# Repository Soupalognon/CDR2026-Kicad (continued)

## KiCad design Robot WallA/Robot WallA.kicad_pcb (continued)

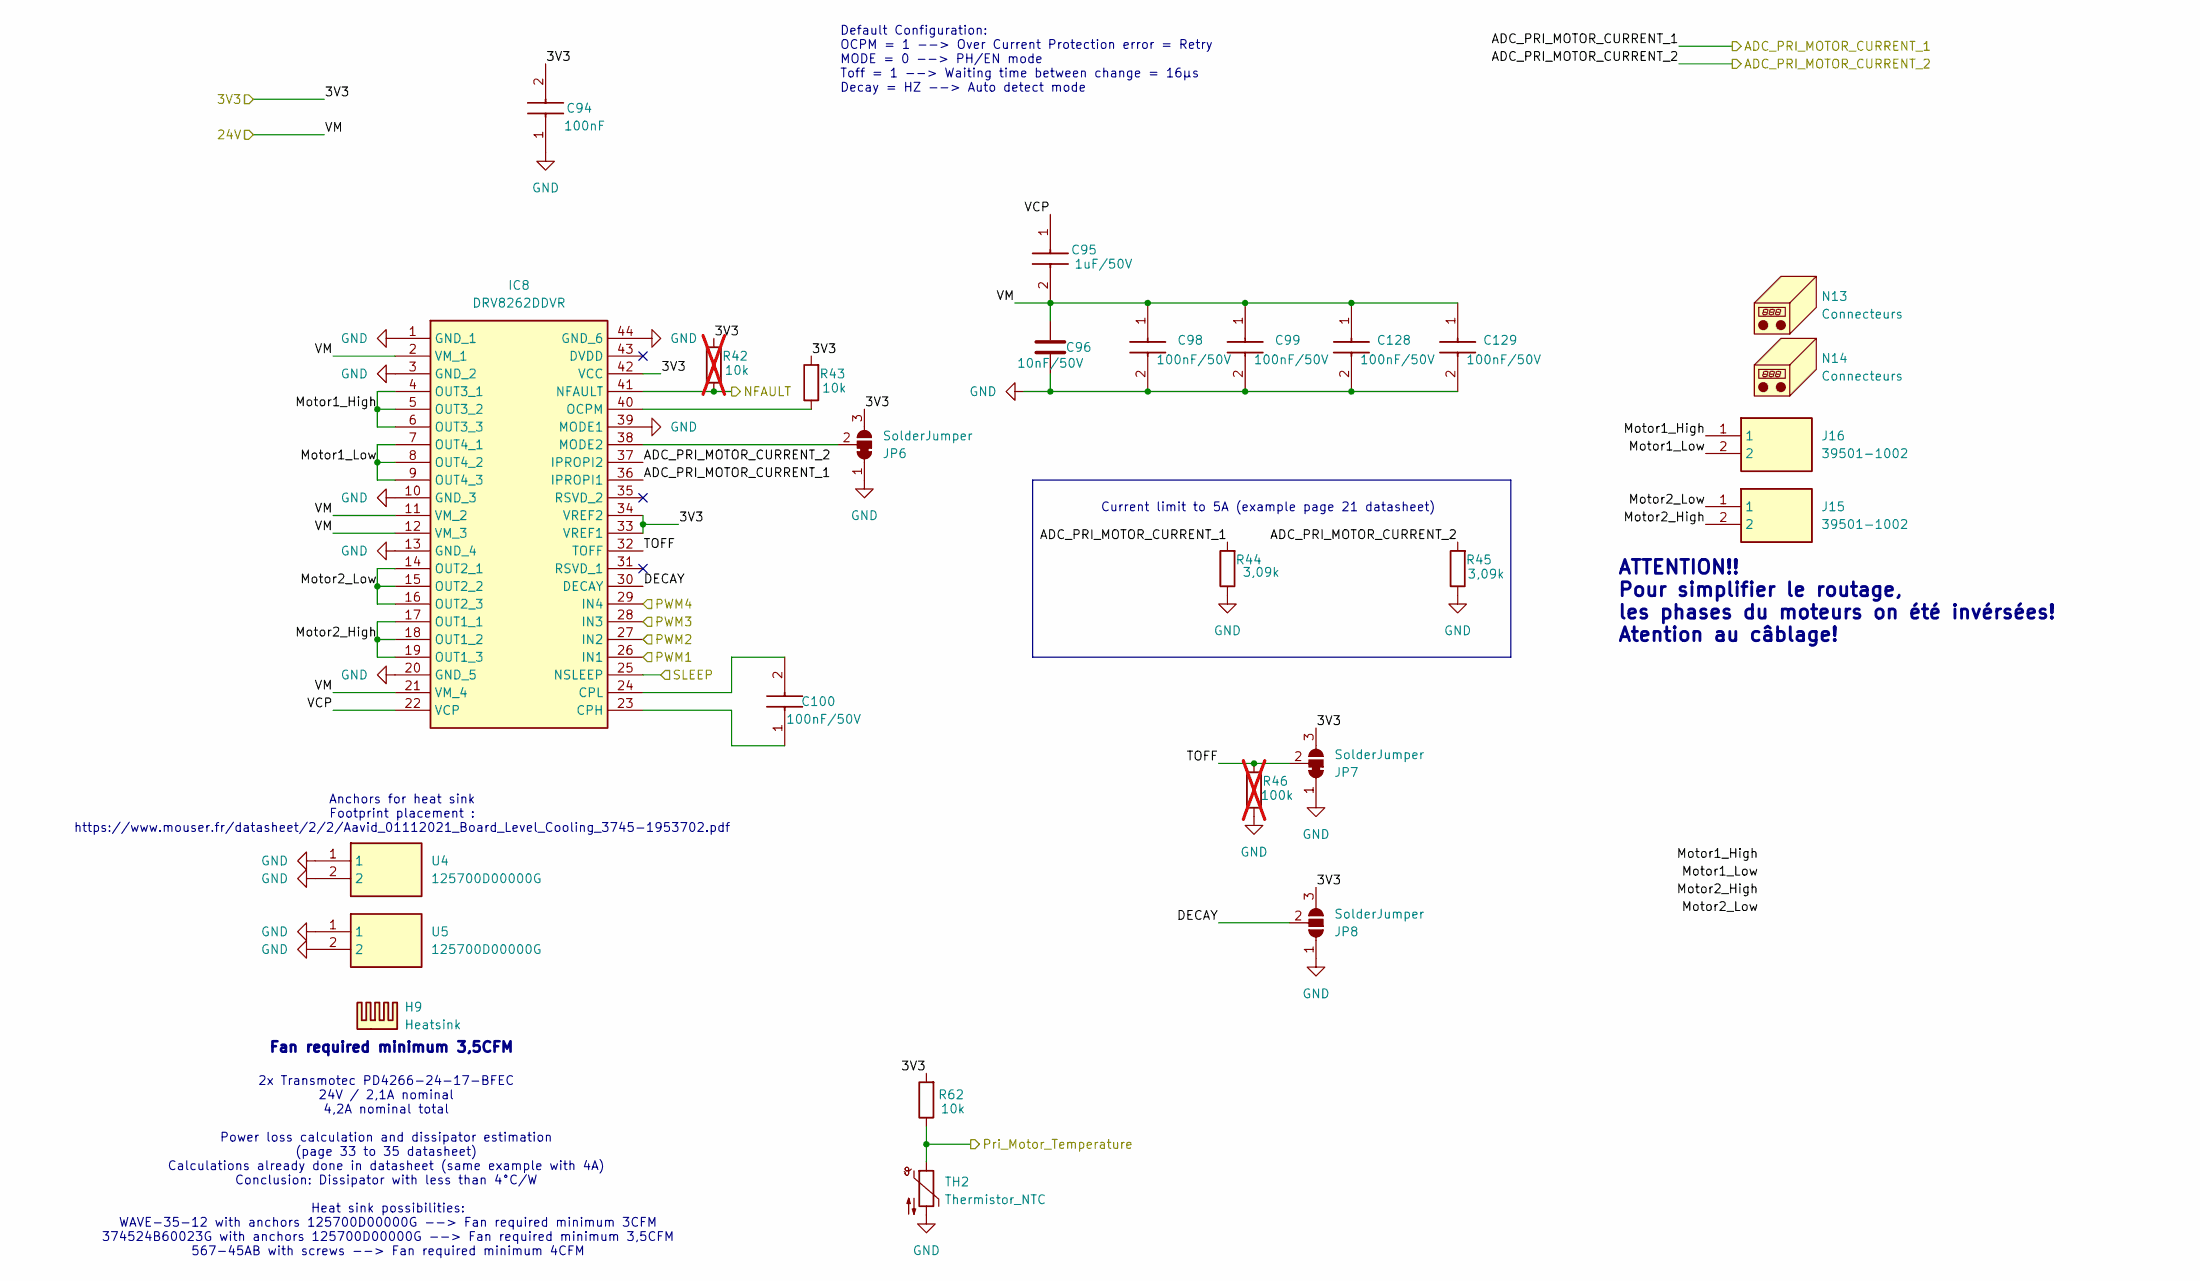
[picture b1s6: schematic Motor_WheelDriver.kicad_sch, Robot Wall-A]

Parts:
C94: 100nF; C_0603_1608Metric_Pad1.08x0.95mm_HandSolder; Manufacturer_Part_Number KGM15BR71H104KT
C95: 1uF/50V; C_0603_1608Metric_Pad1.08x0.95mm_HandSolder; Manufacturer_Part_Number CL10A105KB8NNNC
C96: 10nF/50V; C_0805_2012Metric_Pad1.18x1.45mm_HandSolder; Manufacturer_Part_Number CL21B103KBANNNC
C98, C99, C100, C128, C129: 100nF/50V; C_0603_1608Metric_Pad1.08x0.95mm_HandSolder; Manufacturer_Part_Number KGM15BR71H104KT
H9: Heatsink; 374524B60023G; Manufacturer_Part_Number 374524B60023G
IC8: DRV8262DDVR; SOP64P810X120-44N; Manufacturer_Part_Number DRV8262DDVR
J15, J16: 39501-1002; 395011002; Manufacturer_Part_Number 39501-1002
JP6, JP7: SolderJumper; SolderJumper-3_P1.3mm_Bridged12_Pad1.0x1.5mm
JP8: SolderJumper; SolderJumper-3_P1.3mm_Open_Pad1.0x1.5mm
N13, N14: Connecteurs; Manufacturer_Part_Number 39503-2002
R42: 10k; R_0603_1608Metric_Pad0.98x0.95mm_HandSolder; Manufacturer_Part_Number 667-ERJ-3GEYJ103V; not fitted
R43, R62: 10k; R_0603_1608Metric_Pad0.98x0.95mm_HandSolder; Manufacturer_Part_Number 667-ERJ-3GEYJ103V
R44, R45: 3,09k; R_0603_1608Metric_Pad0.98x0.95mm_HandSolder; Manufacturer_Part_Number CRCW06033K09FKEA
R46: 100k; R_0603_1608Metric_Pad0.98x0.95mm_HandSolder; Manufacturer_Part_Number RCA0603100KFKEAHP; not fitted
TH2: Thermistor_NTC; R_0603_1608Metric_Pad0.98x0.95mm_HandSolder; Manufacturer_Part_Number NCU18XH103E60RB
U4, U5: 125700D00000G; Manufacturer_Part_Number 125700D00000G

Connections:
/MCU/3V3: C94.2, IC8.33 (VREF1), IC8.34 (VREF2), IC8.42 (VCC), JP6.3 (B), JP7.3 (B), JP8.3 (B), R42.2, R43.2, R62.2; also elsewhere on the board
/MCU/WHEEL0: IC8.36 (IPROPI1), R44.2; also elsewhere on the board
/MCU/WHEEL1: IC8.37 (IPROPI2), R45.2; also elsewhere on the board
/MCU/WHEEL2: IC8.26 (IN1); also elsewhere on the board
/MCU/WHEEL3: IC8.27 (IN2); also elsewhere on the board
/MCU/WHEEL4: IC8.28 (IN3); also elsewhere on the board
/MCU/WHEEL5: IC8.29 (IN4); also elsewhere on the board
/MCU/WHEEL6: IC8.41 (NFAULT), R42.1; also elsewhere on the board
/MCU/WHEEL7: IC8.25 (NSLEEP); also elsewhere on the board
/MCU/WHEEL8: R62.1, TH2.1; also elsewhere on the board
/Motor/Motor_WheelDriver/DECAY: IC8.30 (DECAY), JP8.2 (C)
/Motor/Motor_WheelDriver/Motor1_High: IC8.4 (OUT3_1), IC8.5 (OUT3_2), IC8.6 (OUT3_3), J16.1
/Motor/Motor_WheelDriver/Motor1_Low: IC8.7 (OUT4_1), IC8.8 (OUT4_2), IC8.9 (OUT4_3), J16.2
/Motor/Motor_WheelDriver/Motor2_High: IC8.17 (OUT1_1), IC8.18 (OUT1_2), IC8.19 (OUT1_3), J15.2
/Motor/Motor_WheelDriver/Motor2_Low: IC8.14 (OUT2_1), IC8.15 (OUT2_2), IC8.16 (OUT2_3), J15.1
/Motor/Motor_WheelDriver/TOFF: IC8.32 (TOFF), JP7.2 (C), R46.2
/Motor/Motor_WheelDriver/VCP: C95.1, IC8.22 (VCP)
/Power/24V: C95.2, C96.1, C98.1, C99.1, C128.1, C129.1, IC8.2 (VM_1), IC8.11 (VM_2), IC8.12 (VM_3), IC8.21 (VM_4); also elsewhere on the board
GND: C94.1, C96.2, C98.2, C99.2, C128.2, C129.2, IC8.1 (GND_1), IC8.3 (GND_2), IC8.10 (GND_3), IC8.13 (GND_4), IC8.20 (GND_5), IC8.39 (MODE1), IC8.44 (GND_6), JP6.1 (A), JP7.1 (A), JP8.1 (A), R44.1, R45.1, R46.1, TH2.2, U4.1, U4.2, U5.1, U5.2; also elsewhere on the board
unnamed: C100.1, IC8.23 (CPH)
unnamed: C100.2, IC8.24 (CPL)
unnamed: IC8.38 (MODE2), JP6.2 (C)
unnamed: IC8.40 (OCPM), R43.1

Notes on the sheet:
Current limit to 5A (example page 21 datasheet)
Fan required minimum 3,5CFM
Power loss calculation and dissipator estimation (page 33 to 35 datasheet) Calculations already done in datasheet (same example with 4A) Conclusion: Dissipator with less than 4°C/W
Anchors for heat sink Footprint placement : https://www.mouser.fr/datasheet/2/2/Aavid_01112021_Board_Level_Cooling_3745-1953702.pdf
Default Configuration: OCPM = 1 --> Over Current Protection error = Retry MODE = 0 --> PH/EN mode Toff = 1 --> Waiting time between change = 16µs Decay = HZ --> Auto detect mode
ATTENTION!! Pour simplifier le routage, les phases du moteurs on été invérsées! Atention au câblage!
2x Transmotec PD4266-24-17-BFEC 24V / 2,1A nominal 4,2A nominal total
Heat sink possibilities: WAVE-35-12 with anchors 125700D00000G --> Fan required minimum 3CFM 374524B60023G with anchors 125700D00000G --> Fan required minimum 3,5CFM 567-45AB with screws --> Fan required minimum 4CFM

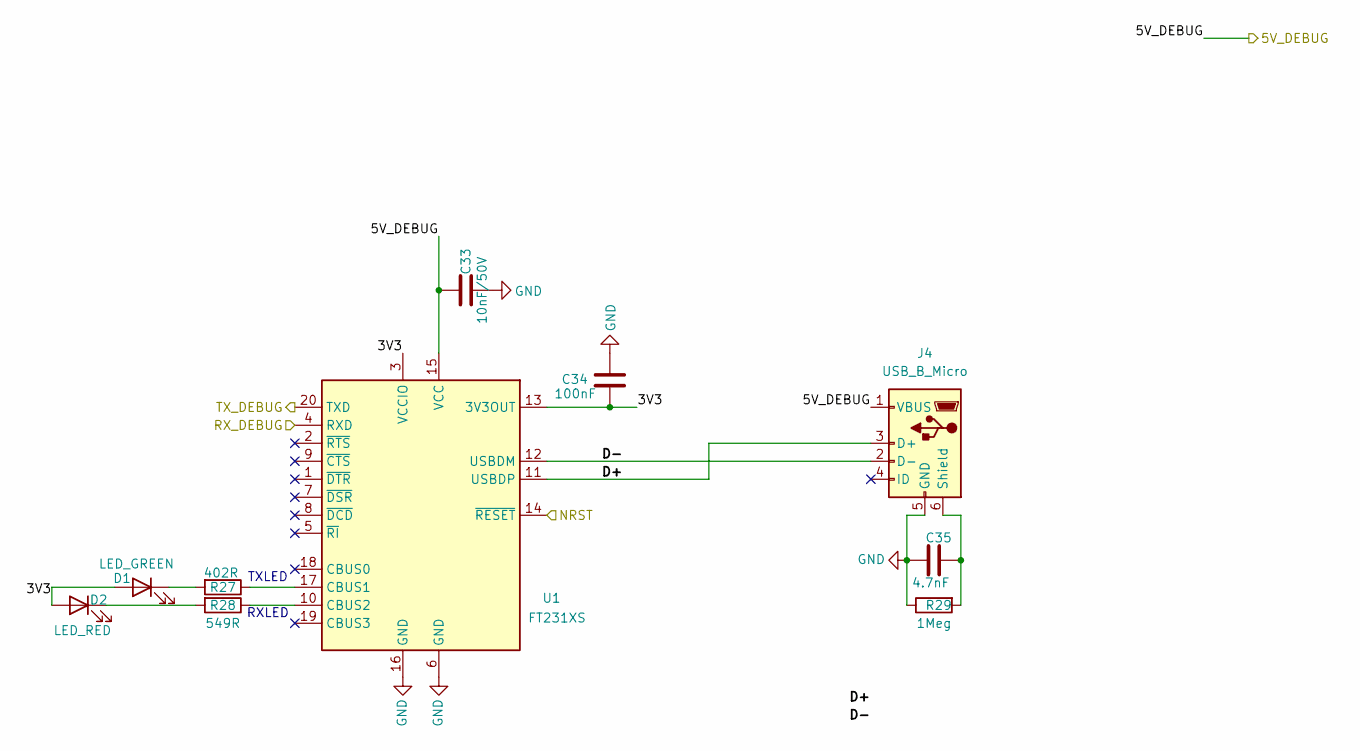
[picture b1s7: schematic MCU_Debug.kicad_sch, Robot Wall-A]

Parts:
C33: 10nF/50V; C_0805_2012Metric_Pad1.18x1.45mm_HandSolder; Manufacturer_Part_Number CL21B103KBANNNC
C34: 100nF; C_0603_1608Metric_Pad1.08x0.95mm_HandSolder; Manufacturer_Part_Number KGM15BR71H104KT
C35: 4.7nF; C_0603_1608Metric_Pad1.08x0.95mm_HandSolder; Manufacturer_Part_Number CC0603JRX7R8BB472
D1: LED_GREEN; LED_0603_1608Metric; Manufacturer_Part_Number APT1608LZGCK
D2: LED_RED; LED_0603_1608Metric; Manufacturer_Part_Number LS L29K-G1J2-1
J4: USB_B_Micro; USB_Micro-B_Molex_47346-0001; Manufacturer_Part_Number USB3140-30-0230-0-C
R27: 402R; R_0603_1608Metric_Pad0.98x0.95mm_HandSolder; Manufacturer_Part_Number CR0603-FX-4020ELF
R28: 549R; R_0603_1608Metric_Pad0.98x0.95mm_HandSolder; Manufacturer_Part_Number RC0603FR-07549RL
R29: 1Meg; R_0603_1608Metric_Pad0.98x0.95mm_HandSolder; Manufacturer_Part_Number ERJ-3GEYJ105V
U1: FT231XS; SSOP-20_3.9x8.7mm_P0.635mm; Manufacturer_Part_Number FT231XS-R

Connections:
/MCU/MCU_Core/NRST: U1.14 (~RESET); also elsewhere on the board
/MCU/MCU_Core/PA9: U1.4 (RXD); also elsewhere on the board
/MCU/MCU_Core/PA10: U1.20 (TXD); also elsewhere on the board
/MCU/MCU_Debug/3V3: C34.1, D1.2 (A), D2.2 (A), U1.3 (VCCIO), U1.13 (3V3OUT)
/MCU/MCU_Debug/5V_DEBUG: C33.1, J4.1 (VBUS), U1.15 (VCC); also elsewhere on the board
/MCU/MCU_Debug/D+: J4.3 (D+), U1.11 (USBDP)
/MCU/MCU_Debug/D-: J4.2 (D-), U1.12 (USBDM)
GND: C33.2, C34.2, C35.2, J4.5 (GND), R29.1, U1.6 (GND), U1.16 (GND); also elsewhere on the board
unnamed: D1.1 (K), R27.2
unnamed: D2.1 (K), R28.2
unnamed: C35.1, J4.6 (Shield), R29.2
unnamed: R27.1, U1.17 (CBUS1)
unnamed: R28.1, U1.10 (CBUS2)

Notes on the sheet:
TXLED
RXLED

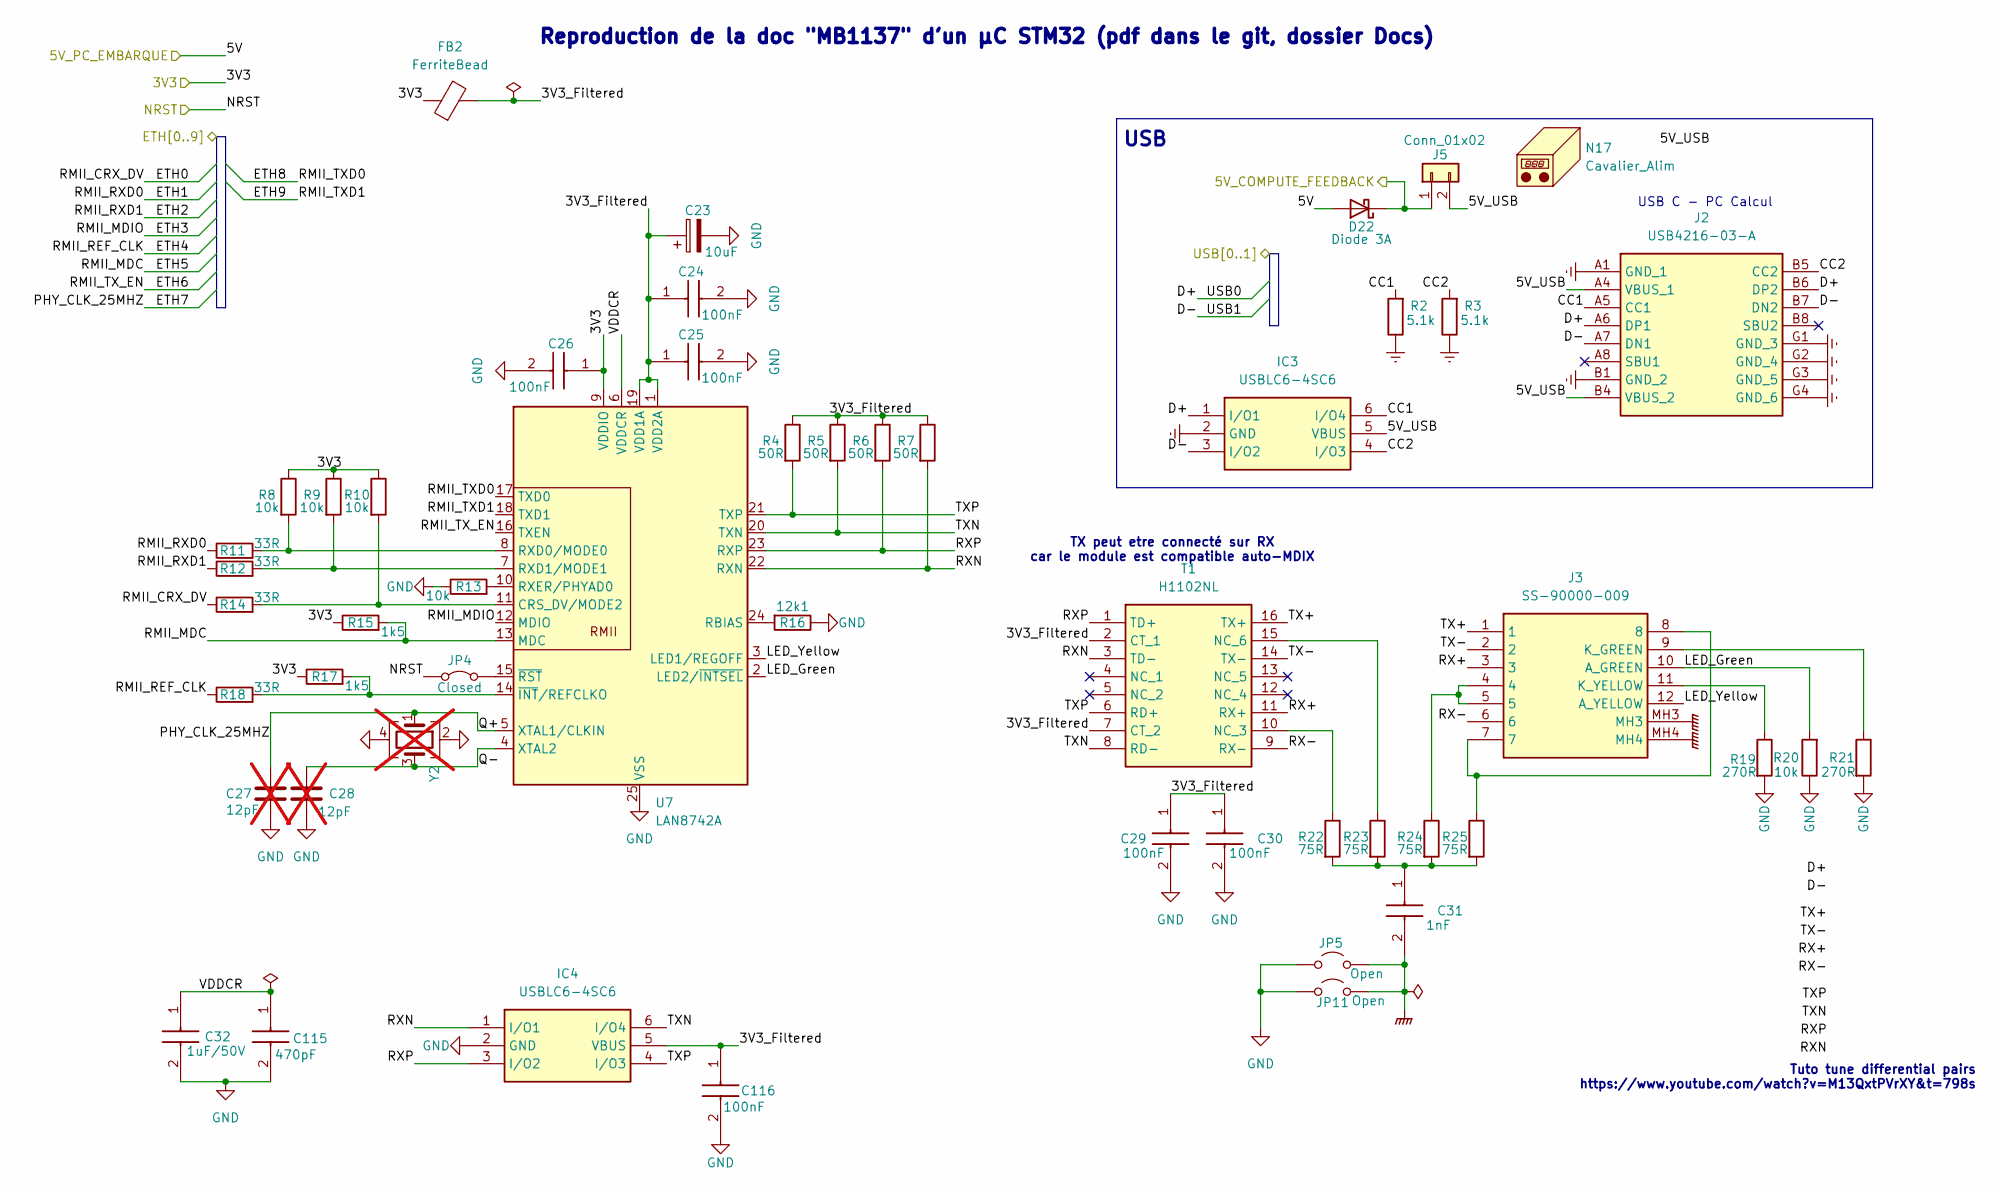
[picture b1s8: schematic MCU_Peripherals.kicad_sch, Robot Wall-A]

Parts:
C23: 10uF; C_1206_3216Metric_Pad1.33x1.80mm_HandSolder; Manufacturer_Part_Number CL31A106KQHNNNE
C24, C25, C26, C29, C30, C116: 100nF; C_0603_1608Metric_Pad1.08x0.95mm_HandSolder; Manufacturer_Part_Number KGM15BR71H104KT
C27, C28: 12pF; C_0603_1608Metric_Pad1.08x0.95mm_HandSolder; Manufacturer_Part_Number C0603C120F5GACTU; not fitted
C31: 1nF; C_1206_3216Metric_Pad1.33x1.80mm_HandSolder; Manufacturer_Part_Number 1206B102K102CT
C32: 1uF/50V; C_0603_1608Metric_Pad1.08x0.95mm_HandSolder; Manufacturer_Part_Number CL10A105KB8NNNC
C115: 470pF; C_0603_1608Metric_Pad1.08x0.95mm_HandSolder; Manufacturer_Part_Number C0603C471K5RACTU
D22: Diode 3A; D_SMP_DO-220AA; Manufacturer_Part_Number SS3P4-M3/84A
FB2: FerriteBead; R_0603_1608Metric_Pad0.98x0.95mm_HandSolder; Manufacturer_Part_Number FCM 1608KF-601T03
IC3, IC4: USBLC6-4SC6; SOT95P280X145-6N; Manufacturer_Part_Number USBLC6-4SC6
J2: USB4216-03-A; USB421603A; Manufacturer_Part_Number USB4216-03-A
J3: SS-90000-009; SS90000009; Manufacturer_Part_Number SS-90000-009
J5: Conn_01x02; PinHeader_1x02_P2.54mm_Vertical
JP4: Closed; SolderJumper-2_P1.3mm_Bridged_RoundedPad1.0x1.5mm
JP5, JP11: Open; SolderJumper-2_P1.3mm_Open_RoundedPad1.0x1.5mm
N17: Cavalier_Alim; Manufacturer_Part_Number 15-29-1024
R2, R3: 5.1k; R_0603_1608Metric_Pad0.98x0.95mm_HandSolder; Manufacturer_Part_Number CRCW06035K10FKEA
R4, R5, R6, R7: 50R; R_0603_1608Metric; Manufacturer_Part_Number CRCW060350R0FKTA
R8, R9, R10, R13, R20: 10k; R_0603_1608Metric_Pad0.98x0.95mm_HandSolder; Manufacturer_Part_Number 667-ERJ-3GEYJ103V
R11, R12, R14, R18: 33R; R_0603_1608Metric_Pad0.98x0.95mm_HandSolder; Manufacturer_Part_Number CRCW060333R0JNEA
R15, R17: 1k5; R_0603_1608Metric_Pad0.98x0.95mm_HandSolder; Manufacturer_Part_Number RC0603JR-071K5L
R16: 12k1; R_0603_1608Metric_Pad0.98x0.95mm_HandSolder; Manufacturer_Part_Number ERJ-3EKF1212V
R19, R21: 270R; R_0603_1608Metric_Pad0.98x0.95mm_HandSolder; Manufacturer_Part_Number RE0603FRE07270RL
R22, R23, R24, R25: 75R; R_0603_1608Metric_Pad0.98x0.95mm_HandSolder; Manufacturer_Part_Number CRCW060375R0FKEAC
T1: H1102NL; SOIC127P940X597-16N; Manufacturer_Part_Number H1102NL
U7: LAN8742A; QFN50P400X400X100-25N-D; Manufacturer_Part_Number LAN8742A-CZ
Y2: Crystal_GND24; Crystal_SMD_3225-4Pin_3.2x2.5mm; Manufacturer_Part_Number ECS-250-10-33B-CWN-TR3; not fitted

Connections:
/MCU/3V3: C26.1, FB2.1, R8.1, R9.1, R10.1, R15.1, R17.1, U7.9 (VDDIO); also elsewhere on the board
/MCU/5V_PC_EMBARQUE: D22.2 (A); also elsewhere on the board
/MCU/MCU_Core/ETH0: R14.1; also elsewhere on the board
/MCU/MCU_Core/ETH1: R11.1; also elsewhere on the board
/MCU/MCU_Core/ETH2: R12.1; also elsewhere on the board
/MCU/MCU_Core/ETH3: U7.12 (MDIO); also elsewhere on the board
/MCU/MCU_Core/ETH4: R18.1; also elsewhere on the board
/MCU/MCU_Core/ETH5: R15.2, U7.13 (MDC); also elsewhere on the board
/MCU/MCU_Core/ETH6: U7.16 (TXEN); also elsewhere on the board
/MCU/MCU_Core/ETH7: C27.1, U7.5 (XTAL1/CLKIN), Y2.1; also elsewhere on the board
/MCU/MCU_Core/ETH8: U7.17 (TXD0); also elsewhere on the board
/MCU/MCU_Core/ETH9: U7.18 (TXD1); also elsewhere on the board
/MCU/MCU_Core/NRST: JP4.1 (A); also elsewhere on the board
/MCU/MCU_Core/USB0: IC3.1 (I/O1), J2.A6 (DP1), J2.B6 (DP2); also elsewhere on the board
/MCU/MCU_Core/USB1: IC3.3 (I/O2), J2.A7 (DN1), J2.B7 (DN2); also elsewhere on the board
/MCU/MCU_Peripherals/3V3_Filtered: C23.1, C24.1, C25.1, C29.1, C30.1, C116.1, FB2.2, IC4.5 (VBUS), R4.1, R5.1, R6.1, R7.1, T1.2 (CT_1), T1.7 (CT_2), U7.1 (VDD2A), U7.19 (VDD1A)
/MCU/MCU_Peripherals/5V_USB: IC3.5 (VBUS), J2.A4 (VBUS_1), J2.B4 (VBUS_2), J5.2
/MCU/MCU_Peripherals/CC1: IC3.6 (I/O4), J2.A5 (CC1), R2.2
/MCU/MCU_Peripherals/CC2: IC3.4 (I/O3), J2.B5 (CC2), R3.2
/MCU/MCU_Peripherals/LED_Green: J3.10 (A_GREEN), R20.2, U7.2 (LED2/~INTSEL)
/MCU/MCU_Peripherals/LED_Yellow: J3.12 (A_YELLOW), U7.3 (LED1/REGOFF)
/MCU/MCU_Peripherals/Q-: C28.1, U7.4 (XTAL2), Y2.3
/MCU/MCU_Peripherals/RX+: J3.3, T1.11 (RX+)
/MCU/MCU_Peripherals/RX-: J3.6, T1.9 (RX-)
/MCU/MCU_Peripherals/RXN: IC4.1 (I/O1), R7.2, T1.3 (TD-), U7.22 (RXN)
/MCU/MCU_Peripherals/RXP: IC4.3 (I/O2), R6.2, T1.1 (TD+), U7.23 (RXP)
/MCU/MCU_Peripherals/TX+: J3.1, T1.16 (TX+)
/MCU/MCU_Peripherals/TX-: J3.2, T1.14 (TX-)
/MCU/MCU_Peripherals/TXN: IC4.6 (I/O4), R5.2, T1.8 (RD-), U7.20 (TXN)
/MCU/MCU_Peripherals/TXP: IC4.4 (I/O3), R4.2, T1.6 (RD+), U7.21 (TXP)
/MCU/MCU_Peripherals/VDDCR: C32.1, C115.1, U7.6 (VDDCR)
/Power/Power_Buck_5V_Compute/5V_sense: D22.1 (K), J5.1; also elsewhere on the board
GND: C23.2, C24.2, C25.2, C26.2, C27.2, C28.2, C29.2, C30.2, C32.2, C115.2, C116.2, IC3.2 (GND), IC4.2 (GND), J2.A1 (GND_1), J2.B1 (GND_2), J2.G1 (GND_3), J2.G2 (GND_4), J2.G3 (GND_5), J2.G4 (GND_6), JP5.2 (B), JP11.2 (B), R2.1, R3.1, R13.1, R16.1, R19.2, R20.1, R21.2, U7.25 (VSS), Y2.2, Y2.4; also elsewhere on the board
GNDPWR: C31.2, J3.MH3, J3.MH4, JP5.1 (A), JP11.1 (A)
unnamed: C31.1, R22.2, R23.2, R24.2, R25.2
unnamed: J3.9 (K_GREEN), R21.1
unnamed: J3.11 (K_YELLOW), R19.1
unnamed: J3.4, J3.5, R24.1
unnamed: J3.7, J3.8, R25.1
unnamed: JP4.2 (B), U7.15 (~RST)
unnamed: R22.1, T1.10 (NC_3)
unnamed: R23.1, T1.15 (NC_6)
unnamed: R10.2, R14.2, U7.11 (CRS_DV/MODE2)
unnamed: R16.2, U7.24 (RBIAS)
unnamed: R8.2, R11.2, U7.8 (RXD0/MODE0)
unnamed: R9.2, R12.2, U7.7 (RXD1/MODE1)
unnamed: R13.2, U7.10 (RXER/PHYAD0)
unnamed: R17.2, R18.2, U7.14 (~INT/REFCLKO)

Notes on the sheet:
USB C - PC Calcul
TX peut etre connecté sur RX car le module est compatible auto-MDIX
Reproduction de la doc "MB1137" d'un µC STM32 (pdf dans le git, dossier Docs)
Tuto tune differential pairs https://www.youtube.com/watch?v=M13QxtPVrXY&t=798s
USB

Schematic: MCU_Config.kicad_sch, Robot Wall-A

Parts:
C3: 4.7uF/50V; C_0805_2012Metric_Pad1.18x1.45mm_HandSolder; Manufacturer_Part_Number GRM21BR61H475ME51L
C4, C5, C6, C7, C8, C9, C10, C11, C12, C13, C14, C15, C16, C17, C18, C19, C22: 100nF; C_0603_1608Metric_Pad1.08x0.95mm_HandSolder; Manufacturer_Part_Number KGM15BR71H104KT
C20, C21: 2.2uF; C_0603_1608Metric_Pad1.08x0.95mm_HandSolder; Manufacturer_Part_Number TMK107ABJ225KA-T
FB1: Bead 600R; R_0603_1608Metric_Pad0.98x0.95mm_HandSolder; Manufacturer_Part_Number FCM 1608KF-601T03
JP1, JP2, JP3: SolderJumper; SolderJumper-3_P1.3mm_Bridged12_Pad1.0x1.5mm
R1: 10k; R_0603_1608Metric_Pad0.98x0.95mm_HandSolder; Manufacturer_Part_Number 667-ERJ-3GEYJ103V; not fitted
SW1: Switch; KMR231NGLFS; Manufacturer_Part_Number KMR231NGLFS

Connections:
/MCU/3V3: C3.1, C4.1, C5.1, C6.1, C7.1, C8.1, C9.1, C10.1, C11.1, C12.1, C13.1, C14.1, C15.1, C16.1, C17.1, C18.1, FB1.1, JP1.3 (B), JP2.3 (B), JP3.1 (A), R1.2; also elsewhere on the board
/MCU/MCU_Config/3V3_ANA: C19.1, FB1.2; also elsewhere on the board
/MCU/MCU_Config/BOOT0: JP1.2 (C); also elsewhere on the board
/MCU/MCU_Config/BYPASS_REG: JP2.2 (C); also elsewhere on the board
/MCU/MCU_Config/PDR_ON: JP3.2 (C); also elsewhere on the board
/MCU/MCU_Config/VCAP_1: C20.1; also elsewhere on the board
/MCU/MCU_Config/VCAP_2: C21.1; also elsewhere on the board
/MCU/MCU_Core/NRST: C22.2, R1.1, SW1.2 (D); also elsewhere on the board
GND: C3.2, C4.2, C5.2, C6.2, C7.2, C8.2, C9.2, C10.2, C11.2, C12.2, C13.2, C14.2, C15.2, C16.2, C17.2, C18.2, C19.2, C20.2, C21.2, C22.1, JP1.1 (A), JP2.1 (A), JP3.3 (B), SW1.1 (C); also elsewhere on the board

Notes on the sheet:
Must be as close as possible from µC

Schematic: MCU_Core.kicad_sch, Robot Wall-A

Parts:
C1, C2: 12pF; C_0603_1608Metric_Pad1.08x0.95mm_HandSolder; Manufacturer_Part_Number C0603C120F5GACTU
D17: LED_YELLOW; LED_0603_1608Metric; Manufacturer_Part_Number SML-D12W8WT86C
D18: LED_ORANGE; LED_0603_1608Metric; Manufacturer_Part_Number CSL1901DW1
D19: LED_GREEN; LED_0603_1608Metric; Manufacturer_Part_Number APT1608LZGCK
D20: LED_BLUE; LED_0603_1608Metric; Manufacturer_Part_Number APT1608LVBC/D
D21: LED_RED; LED_0603_1608Metric; Manufacturer_Part_Number LS L29K-G1J2-1
IC1: STM32F407IGT6; QFP50P2600X2600X160-176N; Manufacturer_Part_Number STM32F407IGT6
IC2: DS04-254-2-04BK-SMT; SOP254P990X430-8N; Manufacturer_Part_Number DS04-254-2-04BK-SMT
J1: Conn_02x05_Female; PinHeader_2x05_P1.27mm_Vertical
R55: 649R; R_0603_1608Metric_Pad0.98x0.95mm_HandSolder; Manufacturer_Part_Number RC0603FR-07649RL
R56: 750R; R_0603_1608Metric_Pad0.98x0.95mm_HandSolder; Manufacturer_Part_Number RC0603FR-10750RL
R57: 324R; R_0603_1608Metric_Pad0.98x0.95mm_HandSolder; Manufacturer_Part_Number RC0603FR-07324RL
R58: 330R; R_0603_1608Metric_Pad0.98x0.95mm_HandSolder; Manufacturer_Part_Number AF0603JR-07330RL
R59: 549R; R_0603_1608Metric_Pad0.98x0.95mm_HandSolder; Manufacturer_Part_Number RC0603FR-07549RL
Y1: Crystal_GND24; Crystal_SMD_3225-4Pin_3.2x2.5mm; Manufacturer_Part_Number ECS-250-10-33B-CWN-TR3

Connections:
/MCU/3V3: D17.2 (A), D18.2 (A), D19.2 (A), D20.2 (A), D21.2 (A), IC1.6 (VBAT), IC1.15 (VDD_1), IC1.23 (VDD_2), IC1.36 (VDD_3), IC1.49 (VDD_4), IC1.62 (VDD_5), IC1.72 (VDD_6), IC1.82 (VDD_7), IC1.91 (VDD_8), IC1.103 (VDD_9), IC1.114 (VDD_10), IC1.127 (VDD_11), IC1.136 (VDD_12), IC1.149 (VDD_13), IC1.159 (VDD_14), IC1.172 (VDD_15), J1.1; also elsewhere on the board
/MCU/ENCODER0: IC1.116 (PC7); also elsewhere on the board
/MCU/ENCODER1: IC1.115 (PC6); also elsewhere on the board
/MCU/ENCODER2: IC1.101 (PD13); also elsewhere on the board
/MCU/ENCODER3: IC1.100 (PD12); also elsewhere on the board
/MCU/MCU_Config/3V3_ANA: IC1.38 (VREF+), IC1.39 (VDDA); also elsewhere on the board
/MCU/MCU_Config/BOOT0: IC1.166 (BOOT0); also elsewhere on the board
/MCU/MCU_Config/BYPASS_REG: IC1.48 (BYPASS_REG); also elsewhere on the board
/MCU/MCU_Config/PDR_ON: IC1.171 (PDR_ON); also elsewhere on the board
/MCU/MCU_Config/VCAP_1: IC1.81 (VCAP_1); also elsewhere on the board
/MCU/MCU_Config/VCAP_2: IC1.125 (VCAP_2); also elsewhere on the board
/MCU/MCU_Core/ETH0: IC1.53 (PA7); also elsewhere on the board
/MCU/MCU_Core/ETH1: IC1.54 (PC4); also elsewhere on the board
/MCU/MCU_Core/ETH2: IC1.55 (PC5); also elsewhere on the board
/MCU/MCU_Core/ETH3: IC1.42 (PA2); also elsewhere on the board
/MCU/MCU_Core/ETH4: IC1.41 (PA1); also elsewhere on the board
/MCU/MCU_Core/ETH5: IC1.33 (PC1); also elsewhere on the board
/MCU/MCU_Core/ETH6: IC1.154 (PG11); also elsewhere on the board
/MCU/MCU_Core/ETH7: IC1.119 (PA8); also elsewhere on the board
/MCU/MCU_Core/ETH8: IC1.92 (PB12); also elsewhere on the board
/MCU/MCU_Core/ETH9: IC1.93 (PB13); also elsewhere on the board
/MCU/MCU_Core/LED_Blue: IC1.4 (PE5), R58.1
/MCU/MCU_Core/LED_Green: IC1.3 (PE4), R57.1
/MCU/MCU_Core/LED_Orange: IC1.1 (PE2), R56.1
/MCU/MCU_Core/LED_Red: IC1.5 (PE6), R59.1
/MCU/MCU_Core/LED_Yellow: IC1.2 (PE3), R55.2
/MCU/MCU_Core/NRST: IC1.31 (NRST), J1.10; also elsewhere on the board
/MCU/MCU_Core/PA0: IC1.40 (PA0); also elsewhere on the board
/MCU/MCU_Core/PA9: IC1.120 (PA9); also elsewhere on the board
/MCU/MCU_Core/PA10: IC1.121 (PA10); also elsewhere on the board
/MCU/MCU_Core/PB6: IC1.164 (PB6); also elsewhere on the board
/MCU/MCU_Core/PB7: IC1.165 (PB7); also elsewhere on the board
/MCU/MCU_Core/PB8: IC1.167 (PB8); also elsewhere on the board
/MCU/MCU_Core/PB9: IC1.168 (PB9); also elsewhere on the board
/MCU/MCU_Core/PD0: IC1.142 (PD0); also elsewhere on the board
/MCU/MCU_Core/PD4: IC1.146 (PD4); also elsewhere on the board
/MCU/MCU_Core/PD7: IC1.151 (PD7); also elsewhere on the board
/MCU/MCU_Core/PE0: IC1.169 (PE0); also elsewhere on the board
/MCU/MCU_Core/PE8: IC1.69 (PE8); also elsewhere on the board
/MCU/MCU_Core/PE12: IC1.75 (PE12); also elsewhere on the board
/MCU/MCU_Core/PF3: IC1.19 (PF3); also elsewhere on the board
/MCU/MCU_Core/PF4: IC1.20 (PF4); also elsewhere on the board
/MCU/MCU_Core/PF5: IC1.21 (PF5); also elsewhere on the board
/MCU/MCU_Core/PF9: IC1.27 (PF9); also elsewhere on the board
/MCU/MCU_Core/PF10: IC1.28 (PF10); also elsewhere on the board
/MCU/MCU_Core/PG7: IC1.111 (PG7); also elsewhere on the board
/MCU/MCU_Core/PG8: IC1.112 (PG8); also elsewhere on the board
/MCU/MCU_Core/PG9: IC1.152 (PG9); also elsewhere on the board
/MCU/MCU_Core/PG12: IC1.155 (PG12); also elsewhere on the board
/MCU/MCU_Core/PG14: IC1.157 (PG14); also elsewhere on the board
/MCU/MCU_Core/PG15: IC1.160 (PG15); also elsewhere on the board
/MCU/MCU_Core/PH13: IC1.128 (PH13); also elsewhere on the board
/MCU/MCU_Core/PI1: IC1.132 (PI1); also elsewhere on the board
/MCU/MCU_Core/PI2: IC1.133 (PI2); also elsewhere on the board
/MCU/MCU_Core/PI3: IC1.134 (PI3); also elsewhere on the board
/MCU/MCU_Core/SWCLK: IC1.137 (PA14), J1.4
/MCU/MCU_Core/SWDIO: IC1.124 (PA13), J1.2
/MCU/MCU_Core/USB0: IC1.123 (PA12); also elsewhere on the board
/MCU/MCU_Core/USB1: IC1.122 (PA11); also elsewhere on the board
/MCU/MCU_Core/UserSwitch_1: IC1.10 (PC15), IC2.5 (NO_1)
/MCU/MCU_Core/UserSwitch_2: IC1.11 (PI9), IC2.6 (NO_2)
/MCU/MCU_Core/UserSwitch_3: IC1.12 (PI10), IC2.7 (NO_3)
/MCU/MCU_Core/UserSwitch_4: IC1.13 (PI11), IC2.8 (NO_4)
/MCU/SECONDARY_MOTOR0: IC1.52 (PA6); also elsewhere on the board
/MCU/SECONDARY_MOTOR1: IC1.56 (PB0); also elsewhere on the board
/MCU/SECONDARY_MOTOR2: IC1.107 (PG3); also elsewhere on the board
/MCU/SECONDARY_MOTOR3: IC1.108 (PG4); also elsewhere on the board
/MCU/SECONDARY_MOTOR4: IC1.109 (PG5); also elsewhere on the board
/MCU/SECONDARY_MOTOR5: IC1.110 (PG6); also elsewhere on the board
/MCU/SECONDARY_MOTOR6: IC1.87 (PH10); also elsewhere on the board
/MCU/SECONDARY_MOTOR7: IC1.88 (PH11); also elsewhere on the board
/MCU/SECONDARY_MOTOR8: IC1.25 (PF7); also elsewhere on the board
/MCU/SENSORS0: IC1.34 (PC2); also elsewhere on the board
/MCU/SENSORS1: IC1.32 (PC0); also elsewhere on the board
/MCU/SENSORS2: IC1.35 (PC3); also elsewhere on the board
/MCU/SENSORS3: IC1.57 (PB1); also elsewhere on the board
/MCU/SENSORS4: IC1.65 (PF15); also elsewhere on the board
/MCU/SENSORS5: IC1.66 (PG0); also elsewhere on the board
/MCU/SENSORS6: IC1.64 (PF14); also elsewhere on the board
/MCU/SENSORS7: IC1.67 (PG1); also elsewhere on the board
/MCU/SENSORS8: IC1.162 (PB4); also elsewhere on the board
/MCU/SENSORS9: IC1.117 (PC8); also elsewhere on the board
/MCU/SENSORS10: IC1.163 (PB5); also elsewhere on the board
/MCU/SENSORS11: IC1.118 (PC9); also elsewhere on the board
/MCU/SENSORS12: IC1.63 (PF13); also elsewhere on the board
/MCU/SENSORS13: IC1.60 (PF12); also elsewhere on the board
/MCU/SENSORS14: IC1.59 (PF11); also elsewhere on the board
/MCU/SENSORS15: IC1.58 (PB2); also elsewhere on the board
/MCU/SERVO0: IC1.150 (PD6); also elsewhere on the board
/MCU/SERVO1: IC1.147 (PD5); also elsewhere on the board
/MCU/SERVO2: IC1.176 (PI7); also elsewhere on the board
/MCU/SERVO3: IC1.51 (PA5); also elsewhere on the board
/MCU/SERVO4: IC1.161 (PB3); also elsewhere on the board
/MCU/SERVO5: IC1.79 (PB10); also elsewhere on the board
/MCU/SERVO6: IC1.80 (PB11); also elsewhere on the board
/MCU/WHEEL0: IC1.47 (PA3); also elsewhere on the board
/MCU/WHEEL1: IC1.50 (PA4); also elsewhere on the board
/MCU/WHEEL2: IC1.70 (PE9); also elsewhere on the board
/MCU/WHEEL3: IC1.74 (PE11); also elsewhere on the board
/MCU/WHEEL4: IC1.76 (PE13); also elsewhere on the board
/MCU/WHEEL5: IC1.77 (PE14); also elsewhere on the board
/MCU/WHEEL6: IC1.18 (PF2); also elsewhere on the board
/MCU/WHEEL7: IC1.17 (PF1); also elsewhere on the board
/MCU/WHEEL8: IC1.24 (PF6); also elsewhere on the board
/Power/GPIO_ENABLE_POWER_SUPPLIES: IC1.95 (PB15); also elsewhere on the board
/Power/GPIO_PGOOD: IC1.94 (PB14); also elsewhere on the board
/Power/Temperature: IC1.26 (PF8); also elsewhere on the board
GND: C1.2, C2.2, IC1.14 (VSS_1), IC1.22 (VSS_2), IC1.37 (VSSA), IC1.61 (VSS_3), IC1.71 (VSS_4), IC1.90 (VSS_5), IC1.102 (VSS_6), IC1.113 (VSS_7), IC1.126 (VSS_8), IC1.135 (VSS_9), IC1.148 (VSS_10), IC1.158 (VSS_11), IC2.1 (COM_1), IC2.2 (COM_2), IC2.3 (COM_3), IC2.4 (COM_4), J1.3, J1.5, Y1.2, Y1.4; also elsewhere on the board
unnamed: D17.1 (K), R55.1
unnamed: D18.1 (K), R56.2
unnamed: D19.1 (K), R57.2
unnamed: D20.1 (K), R58.2
unnamed: D21.1 (K), R59.2
unnamed: C1.1, IC1.29 (PH0), Y1.1
unnamed: C2.1, IC1.30 (PH1), Y1.3

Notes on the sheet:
Program
USB --> PC CALCUL ETHERNET --> PC CALCUL UART1 --> DEBUG UART2 --> SERVOMOTEURS
Pour calculer la valeurs des condo autour du Quartz: Application note an2867 page 13
USER INTERFACE
DEBUG LEDs

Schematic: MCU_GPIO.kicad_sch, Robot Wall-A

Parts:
J6, J13: 10129383-916001ALF; 10129383916001ALF; Manufacturer_Part_Number 10129383-916001ALF

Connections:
/MCU/3V3: J6.A1, J6.B1; also elsewhere on the board
/MCU/MCU_Core/PA0: J6.A8; also elsewhere on the board
/MCU/MCU_Core/PA9: J6.A5; also elsewhere on the board
/MCU/MCU_Core/PA10: J6.B5; also elsewhere on the board
/MCU/MCU_Core/PB6: J13.B6; also elsewhere on the board
/MCU/MCU_Core/PB7: J13.A6; also elsewhere on the board
/MCU/MCU_Core/PB8: J13.B7; also elsewhere on the board
/MCU/MCU_Core/PB9: J13.A7; also elsewhere on the board
/MCU/MCU_Core/PD0: J13.B2; also elsewhere on the board
/MCU/MCU_Core/PD4: J13.B3; also elsewhere on the board
/MCU/MCU_Core/PD7: J13.A3; also elsewhere on the board
/MCU/MCU_Core/PE0: J13.B8; also elsewhere on the board
/MCU/MCU_Core/PE8: J6.B4; also elsewhere on the board
/MCU/MCU_Core/PE12: J6.A4; also elsewhere on the board
/MCU/MCU_Core/PF3: J13.A8; also elsewhere on the board
/MCU/MCU_Core/PF4: J6.B7; also elsewhere on the board
/MCU/MCU_Core/PF5: J6.B8; also elsewhere on the board
/MCU/MCU_Core/PF9: J6.A6; also elsewhere on the board
/MCU/MCU_Core/PF10: J6.A7; also elsewhere on the board
/MCU/MCU_Core/PG7: J6.A3; also elsewhere on the board
/MCU/MCU_Core/PG8: J6.B3; also elsewhere on the board
/MCU/MCU_Core/PG9: J13.B4; also elsewhere on the board
/MCU/MCU_Core/PG12: J13.A4; also elsewhere on the board
/MCU/MCU_Core/PG14: J13.B5; also elsewhere on the board
/MCU/MCU_Core/PG15: J13.A5; also elsewhere on the board
/MCU/MCU_Core/PH13: J6.B6; also elsewhere on the board
/MCU/MCU_Core/PI1: J13.A1; also elsewhere on the board
/MCU/MCU_Core/PI2: J13.A2; also elsewhere on the board
/MCU/MCU_Core/PI3: J13.B1; also elsewhere on the board
GND: J6.A2, J6.B2; also elsewhere on the board

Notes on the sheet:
DEBUG UART RX -> PA10 TX -> PA9 I2C1 SDA -> PB7 SCL -> PB6 SPI2 MISO -> PI2 MOSI -> PI3 SCK -> PI1 UART6 RX -> PG9 TX -> PG14 CAN1 RX -> PD0 TX ->PH13

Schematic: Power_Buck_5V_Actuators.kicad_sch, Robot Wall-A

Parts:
C86: 100uF; CAPPRD350W65D800H1250; Manufacturer_Part_Number EEU-FC1V101
C87, C118, C124, C125: 4.7uF/50V; C_1210_3225Metric_Pad1.33x2.70mm_HandSolder; Manufacturer_Part_Number GRM32ER71H475KA88L
C119: 10nF/50V; C_0805_2012Metric_Pad1.18x1.45mm_HandSolder; Manufacturer_Part_Number CL21B103KBANNNC
C120: 2.2uF/50V; C_1210_3225Metric_Pad1.33x2.70mm_HandSolder; Manufacturer_Part_Number C3225X7R1H225K250AB
C121, C122, C123: 47nF/50V; C_0603_1608Metric_Pad1.08x0.95mm_HandSolder; Manufacturer_Part_Number CC0603KPX7R9BB473
D5: LED_RED; LED_0603_1608Metric; Manufacturer_Part_Number LS L29K-G1J2-1
JP12: Closed; SolderJumper-2_P1.3mm_Bridged_RoundedPad1.0x1.5mm
JP13: Open; SolderJumper-2_P1.3mm_Open_RoundedPad1.0x1.5mm
Q6: BSS138; SOT-23; Manufacturer_Part_Number BSS138
R30: 1.6k; R_0603_1608Metric_Pad0.98x0.95mm_HandSolder; Manufacturer_Part_Number ERJ-3EKF1601V
R54: 21k; R_0603_1608Metric_Pad0.98x0.95mm_HandSolder; Manufacturer_Part_Number RC0603FR-0721KL
R60: 10k; R_0603_1608Metric_Pad0.98x0.95mm_HandSolder; Manufacturer_Part_Number 667-ERJ-3GEYJ103V; not fitted
RV3: Trim 2k; TC42X2202E; Manufacturer_Part_Number TC42X-2-202E; not fitted
U9: PTN78060W_EUW-7; Texas_EUW_R-PDSS-T7_THT; Manufacturer_Part_Number PTN78060WAD

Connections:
/Motor/5V: C86.1, C87.1, C118.1, C119.1, D5.2 (A), U9.5 (VO_Sense), U9.6 (VO); also elsewhere on the board
/Power/GPIO_ENABLE_POWER_SUPPLIES: Q6.1 (G), R60.1; also elsewhere on the board
/Power/Power_Buck_5V_Actuators/IN: C120.1, C121.1, C122.1, C123.1, C124.1, C125.1, U9.2 (VI); also elsewhere on the board
/Power/Power_Buck_5V_Actuators/TRIM: R54.1, U9.4 (VO_Adj)
GND: C86.2, C87.2, C118.2, C119.2, C120.2, C121.2, C122.2, C123.2, C124.2, C125.2, JP12.1 (A), Q6.2 (S), R30.2, R60.2, RV3.2, U9.1 (GND), U9.7 (GND); also elsewhere on the board
unnamed: D5.1 (K), R30.1
unnamed: JP12.2 (B), JP13.1 (A), R54.2
unnamed: JP13.2 (B), RV3.1
unnamed: Q6.3 (D), U9.3 (~Inhibit)

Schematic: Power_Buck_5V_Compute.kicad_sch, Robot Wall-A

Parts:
C51: 100uF; CAPPRD350W65D800H1250; Manufacturer_Part_Number EEU-FC1V101
C52, C53, C59, C60: 4.7uF/50V; C_1210_3225Metric_Pad1.33x2.70mm_HandSolder; Manufacturer_Part_Number GRM32ER71H475KA88L
C54: 10nF/50V; C_0805_2012Metric_Pad1.18x1.45mm_HandSolder; Manufacturer_Part_Number CL21B103KBANNNC
C55: 2.2uF/50V; C_1210_3225Metric_Pad1.33x2.70mm_HandSolder; Manufacturer_Part_Number C3225X7R1H225K250AB
C56, C57, C58: 47nF/50V; C_0603_1608Metric_Pad1.08x0.95mm_HandSolder; Manufacturer_Part_Number CC0603KPX7R9BB473
D16: LED_RED; LED_0603_1608Metric; Manufacturer_Part_Number LS L29K-G1J2-1
JP14: Closed; SolderJumper-2_P1.3mm_Bridged_RoundedPad1.0x1.5mm
JP15: Open; SolderJumper-2_P1.3mm_Open_RoundedPad1.0x1.5mm
R31: 1.6k; R_0603_1608Metric_Pad0.98x0.95mm_HandSolder; Manufacturer_Part_Number ERJ-3EKF1601V
R32: 21k; R_0603_1608Metric_Pad0.98x0.95mm_HandSolder; Manufacturer_Part_Number RC0603FR-0721KL
RV2: Trim 2k; TC42X2202E; Manufacturer_Part_Number TC42X-2-202E; not fitted
U10: PTN78060W_EUW-7; Texas_EUW_R-PDSS-T7_THT; Manufacturer_Part_Number PTN78060WAD

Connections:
/MCU/5V_PC_EMBARQUE: C51.1, C52.1, C53.1, C54.1, D16.2 (A), U10.6 (VO); also elsewhere on the board
/Power/Power_Buck_5V_Compute/5V_sense: U10.5 (VO_Sense); also elsewhere on the board
/Power/Power_Buck_5V_Compute/IN: C55.1, C56.1, C57.1, C58.1, C59.1, C60.1, U10.2 (VI); also elsewhere on the board
/Power/Power_Buck_5V_Compute/TRIM: R32.1, U10.4 (VO_Adj)
GND: C51.2, C52.2, C53.2, C54.2, C55.2, C56.2, C57.2, C58.2, C59.2, C60.2, JP14.1 (A), R31.2, RV2.2, U10.1 (GND), U10.7 (GND); also elsewhere on the board
unnamed: D16.1 (K), R31.1
unnamed: JP14.2 (B), JP15.1 (A), R32.2
unnamed: JP15.2 (B), RV2.1
unnamed 205: U10.3 (~Inhibit); also elsewhere on the board
